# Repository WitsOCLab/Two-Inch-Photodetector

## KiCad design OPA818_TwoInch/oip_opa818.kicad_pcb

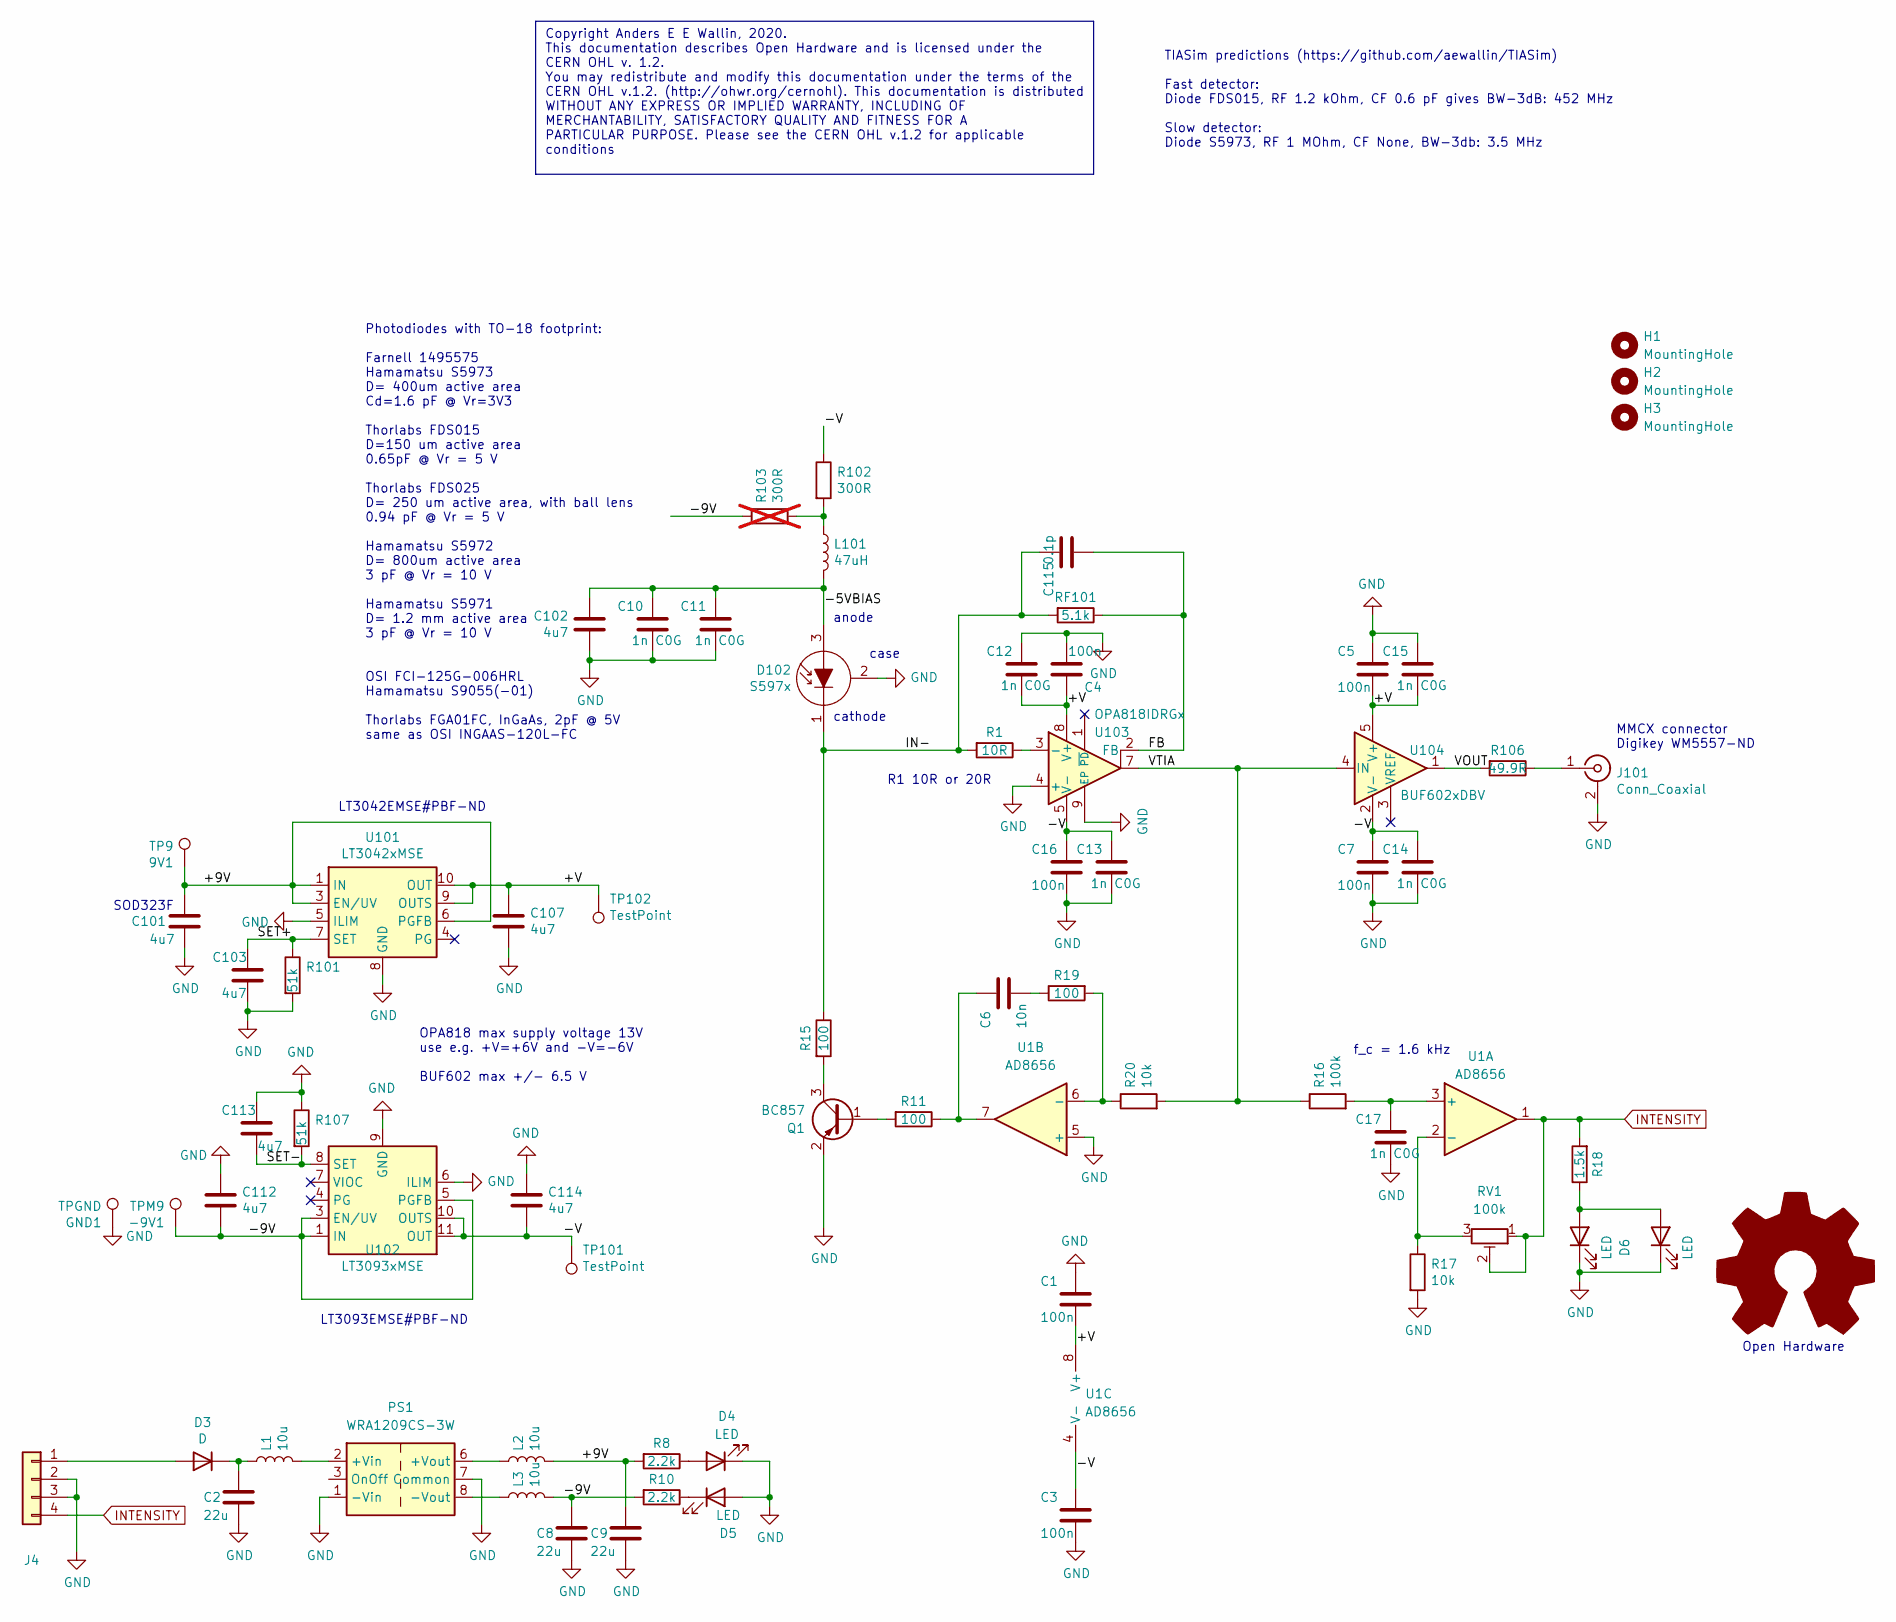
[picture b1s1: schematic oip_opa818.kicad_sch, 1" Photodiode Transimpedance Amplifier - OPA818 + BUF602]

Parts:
9V1: TP9; TestPoint_THTPad_D1.0mm_Drill0.5mm
-9V1: TPM9; TestPoint_THTPad_D1.0mm_Drill0.5mm
C1, C3, C4, C5, C7, C16: 100n; C_0402_1005Metric; JLCPCB C307331
C2, C8, C9: 22u; C_0805_2012Metric; JLCPCB C45783
C6: 10n; C_0402_1005Metric; LCSC C15195
C10, C11, C12, C13, C14, C15, C17: 1n C0G; C_0402_1005Metric; JLCPCB C76947
C101, C102, C103, C107, C112, C113, C114: 4u7; C_0603_1608Metric; JLCPCB C19666
C115: 0.1p; C_0402_1005Metric; LCSC C53273
D3: D; D_SOD-323F; JLCPCB C191023
D4, D5, D6, D7: LED; LED_0603_1608Metric; JLCPCB C72043
D102: S597x; TO-18-3
GND1: TPGND; TestPoint_THTPad_D1.0mm_Drill0.5mm
H1, H2, H3: MountingHole; MountingHole_3.2mm_M3_DIN965_Pad_TopBottom
J4: PinHeader_1x04_P2.54mm_Vertical
J101: Conn_Coaxial; MMCX_Molex_73415-1471_Vertical; JLCPCB C530664
L1, L2, L3: 10u; L_0805_2012Metric; JLCPCB C281113
L101: 47uH; L_0805_2012Metric; LCSC C404762
PS1: WRA1209CS-3W; Converter_DCDC_XP_POWER-ITQxxxxS-H_THT; LCSC C512079
Q1: BC857; SOT-323_SC-70; LCSC C8660
R1: 10R; R_0402_1005Metric; JLCPCB C25077
R8, R10: 2.2k; R_0402_1005Metric; JLCPCB C25879
R11, R15, R19: 100; R_0402_1005Metric; JLCPCB C25076
R16: 100k; R_0402_1005Metric; LCSC C25741
R17, R20: 10k; R_0402_1005Metric; LCSC C25744
R18: 1.5k; R_0603_1608Metric; LCSC C22843
R101, R107: 51k; R_0603_1608Metric; JLCPCB C23186
R102: 300R; R_0603_1608Metric; JLCPCB C23025
R103: 300R; R_0603_1608Metric; JLCPCB C23025; not fitted
R106: 49.9R; R_0402_1005Metric; JLCPCB C25120
RF101: 5.1k; R_0402_1005Metric; JLCPCB C351692
RV1: 100k; Potentiometer_Bourns_TC33X_Vertical; LCSC C719186
TP101, TP102: TestPoint; TestPoint_THTPad_D1.0mm_Drill0.5mm
U1: AD8656; MSOP-8_3x3mm_P0.65mm; LCSC C208582
U101: LT3042xMSE; MSOP-10-1EP_3x3mm_P0.5mm_EP1.68x1.88mm; LCSC C69847
U102: LT3093xMSE; MSOP-12-1EP_3x4mm_P0.65mm_EP1.65x2.85mm; LCSC C670490
U103: OPA818IDRGx; WSON-8-1EP_3x3mm_P0.5mm_EP1.45x2.4mm; JLCPCB C2859543
U104: BUF602xDBV; SOT-23-5; LCSC C2862949

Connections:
/+9V: 9V1.1, C9.1, C101.1, L2.2, R8.2, U101.1 (IN), U101.2 (IN), U101.3 (EN/UV), U101.6 (PGFB)
/+V: C1.2, C4.1, C5.2, C12.2, C15.2, C107.1, TP102.1, U1.8 (V+), U101.9 (OUTS), U101.10 (OUT), U103.8 (V+), U104.5 (V+)
/-5VBIAS: C10.1, C11.1, C102.1, D102.3 (A), L101.2
/-9V: -9V1.1, C8.1, C112.2, L3.2, R10.2, R103.1, U102.1 (IN), U102.2 (IN), U102.3 (EN/UV), U102.5 (PGFB), U102.13 (IN)
/-V: C3.1, C7.1, C13.1, C14.1, C16.1, C114.2, R102.1, TP101.1, U1.4 (V-), U102.10 (OUTS), U102.11 (OUT), U102.12 (OUT), U103.5 (V-), U104.2 (V-)
/FB: C115.1, RF101.1, U103.2 (FB)
/IN-: C115.2, D102.1 (K), R1.2, R15.1, RF101.2
/SET+: C103.1, R101.1, U101.7 (SET)
/SET-: C113.2, R107.2, U102.8 (SET)
/VOUT: R106.2, U104.1
/VTIA: R16.1, R20.2, U103.7, U104.4 (IN)
GND: C1.1, C2.2, C3.2, C4.2, C5.1, C7.2, C8.2, C9.2, C10.2, C11.2, C12.1, C13.2, C14.2, C15.1, C16.2, C17.2, C101.2, C102.2, C103.2, C107.2, C112.1, C113.1, C114.1, D4.1 (K), D5.2 (A), D6.1 (K), D7.1 (K), D102.2 (C), GND1.1, J4.2, J4.3, J101.2 (Ext), PS1.1 (-Vin), PS1.7 (Common), Q1.2 (E), R17.2, R101.2, R107.1, U1.5 (+), U101.5 (ILIM), U101.8 (GND), U101.11 (GND), U102.6 (ILIM), U102.9 (GND), U103.4 (+), U103.9 (EP)
INTENSITY: J4.4, R18.2, RV1.1, RV1.2, U1.1
unnamed: C6.1, R11.1, U1.7
unnamed: C6.2, R19.1
unnamed: D3.2 (A), J4.1
unnamed: C2.1, D3.1 (K), L1.1
unnamed: D4.2 (A), R8.1
unnamed: D5.1 (K), R10.1
unnamed: D6.2 (A), D7.2 (A), R18.1
unnamed: J101.1 (In), R106.1
unnamed: L101.1, R102.2, R103.2
unnamed: L1.2, PS1.2 (+Vin)
unnamed: L2.1, PS1.6 (+Vout)
unnamed: L3.1, PS1.8 (-Vout)
unnamed: Q1.1 (B), R11.2
unnamed: Q1.3 (C), R15.2
unnamed: C17.1, R16.2, U1.3 (+)
unnamed: R17.1, RV1.3, U1.2 (-)
unnamed: R19.2, R20.1, U1.6 (-)
unnamed: R1.1, U103.3 (-)

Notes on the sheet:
LT3042EMSE#PBF-ND
TIASim predictions (https://github.com/aewallin/TIASim) Fast detector: Diode FDS015, RF 1.2 kOhm, CF 0.6 pF gives BW-3dB: 452 MHz Slow detector: Diode S5973, RF 1 MOhm, CF None, BW-3db: 3.5 MHz
cathode
MMCX connector Digikey WM5557-ND
case
R1 10R or 20R
Open Hardware
Photodiodes with TO-18 footprint: Farnell 1495575 Hamamatsu S5973 D= 400um active area Cd=1.6 pF @ Vr=3V3 Thorlabs FDS015 D=150 um active area 0.65pF @ Vr = 5 V Thorlabs FDS025 D= 250 um active area, with ball lens 0.94 pF @ Vr = 5 V Hamamatsu S5972 D= 800um active area 3 pF @ Vr = 10 V Hamamatsu S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
OPA818 max supply voltage 13V use e.g. +V=+6V and -V=-6V BUF602 max +/- 6.5 V
Copyright Anders E E Wallin, 2020. This documentation describes Open Hardware and is licensed under the CERN OHL v. 1.2. You may redistribute and modify this documentation under the terms of the CERN OHL v.1.2. (http://ohwr.org/cernohl). This documentation is distributed WITHOUT ANY EXPRESS OR IMPL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
f_c = 1.6 kHz
anode
LT3093EMSE#PBF-ND
SOD323F

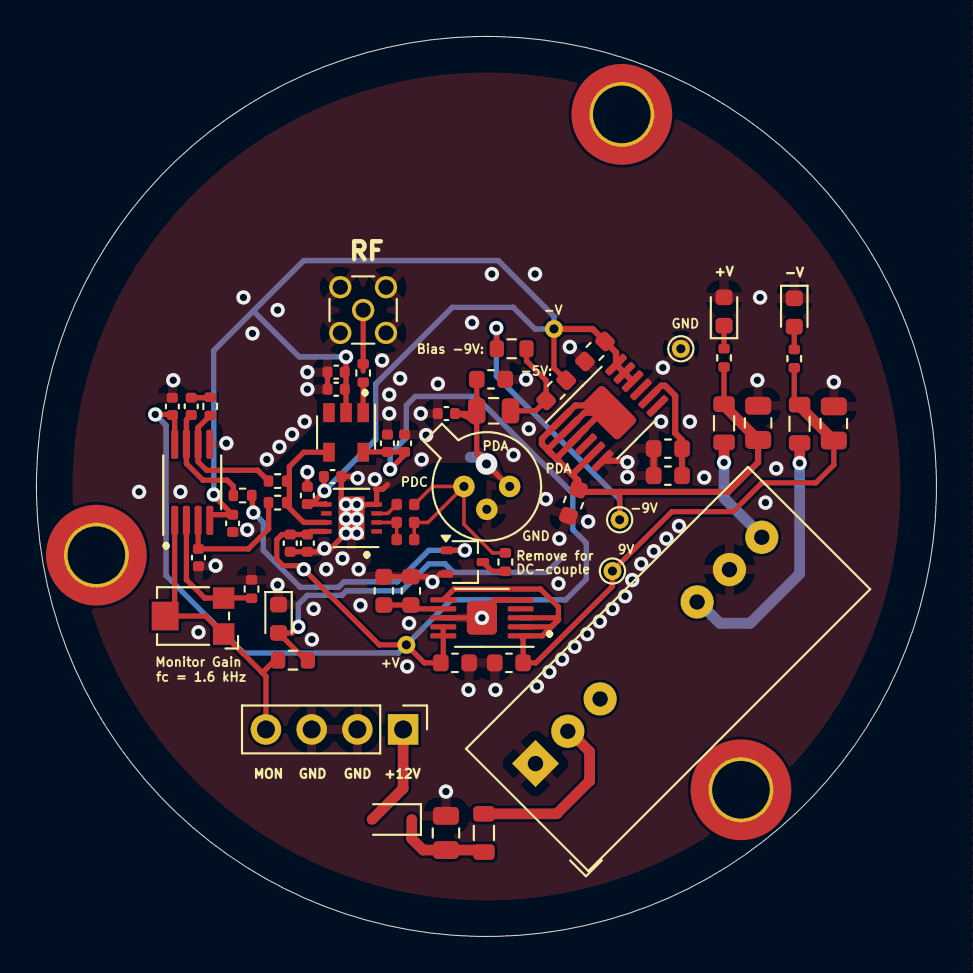
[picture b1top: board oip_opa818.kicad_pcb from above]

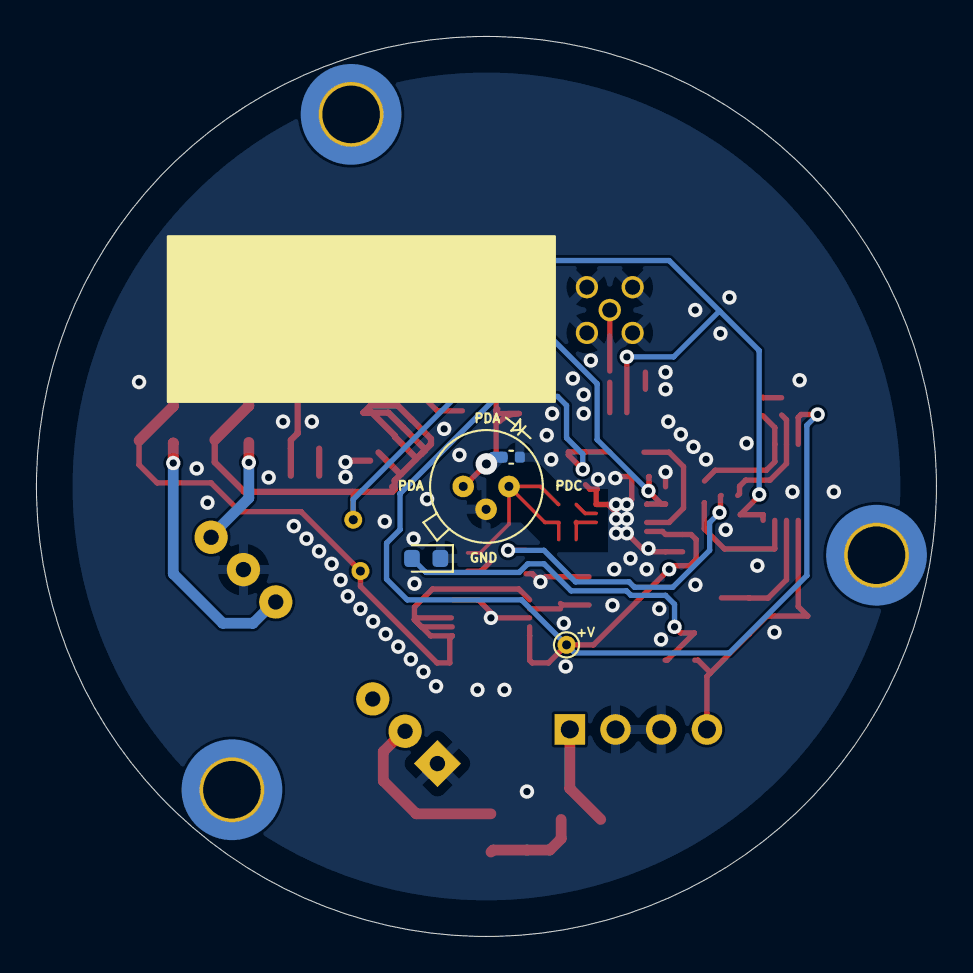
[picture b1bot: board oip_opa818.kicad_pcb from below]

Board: 2 copper layers, 50.0 x 50.0 mm, 69 parts (4 on the bottom side), 31 nets.

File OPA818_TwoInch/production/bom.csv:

Designator,Footprint,Quantity,Value,LCSC Part #
-9V1,TestPoint_THTPad_D1.0mm_Drill0.5mm,1,TPM9,
9V1,TestPoint_THTPad_D1.0mm_Drill0.5mm,1,TP9,
"C1, C16, C3, C4, C5, C7",0402,6,100n,C307331
"C10, C11, C12, C13, C14, C15, C17",0402,7,1n C0G,C76947
"C101, C102, C103, C107, C112, C113, C114",0603,7,4u7,C19666
C115,0402,1,0.1p,C53273
"C2, C8, C9",0805,3,22u,C45783
C6,0402,1,10n,C15195
D102,TO-18-3,1,S597x,
D3,D_SOD-323F,1,D,C191023
"D4, D5, D6, D7",0603,4,LED,C72043
GND1,TestPoint_THTPad_D1.0mm_Drill0.5mm,1,TPGND,
J101,MMCX_Molex_73415-1471_Vertical,1,Conn_Coaxial,C530664
J4,PinHeader_1x04_P2.54mm_Vertical,1,~,
"L1, L2, L3",0805,3,10u,C281113
L101,0805,1,47uH,C404762
PS1,Converter_DCDC_XP_POWER-ITQxxxxS-H_THT,1,WRA1209CS-3W,C512079
Q1,SOT-323_SC-70,1,BC857,C8660
R1,0402,1,10R,C25077
"R10, R8",0402,2,2.2k,C25879
"R101, R107",0603,2,51k,C23186
R102,0603,1,300R,C23025
R106,0402,1,49.9R,C25120
"R11, R15, R19",0402,3,100,C25076
R16,0402,1,100k,C25741
"R17, R20",0402,2,10k,C25744
R18,0603,1,1.5k,C22843
RF101,0402,1,5.1k,C351692
RV1,Potentiometer_Bourns_TC33X_Vertical,1,100k,C719186
"TP101, TP102",TestPoint_THTPad_D1.0mm_Drill0.5mm,2,TestPoint,
U1,MSOP-8_3x3mm_P0.65mm,1,AD8656,C208582
U101,MSOP-10-1EP_3x3mm_P0.5mm_EP1.68x1.88mm,1,LT3042xMSE,C69847
U102,MSOP-12-1EP_3x4mm_P0.65mm_EP1.65x2.85mm,1,LT3093xMSE,C670490
U103,WSON-8-1EP_3x3mm_P0.5mm_EP1.45x2.4mm,1,OPA818IDRGx,C2859543
U104,SOT-23-5,1,BUF602xDBV,C2862949

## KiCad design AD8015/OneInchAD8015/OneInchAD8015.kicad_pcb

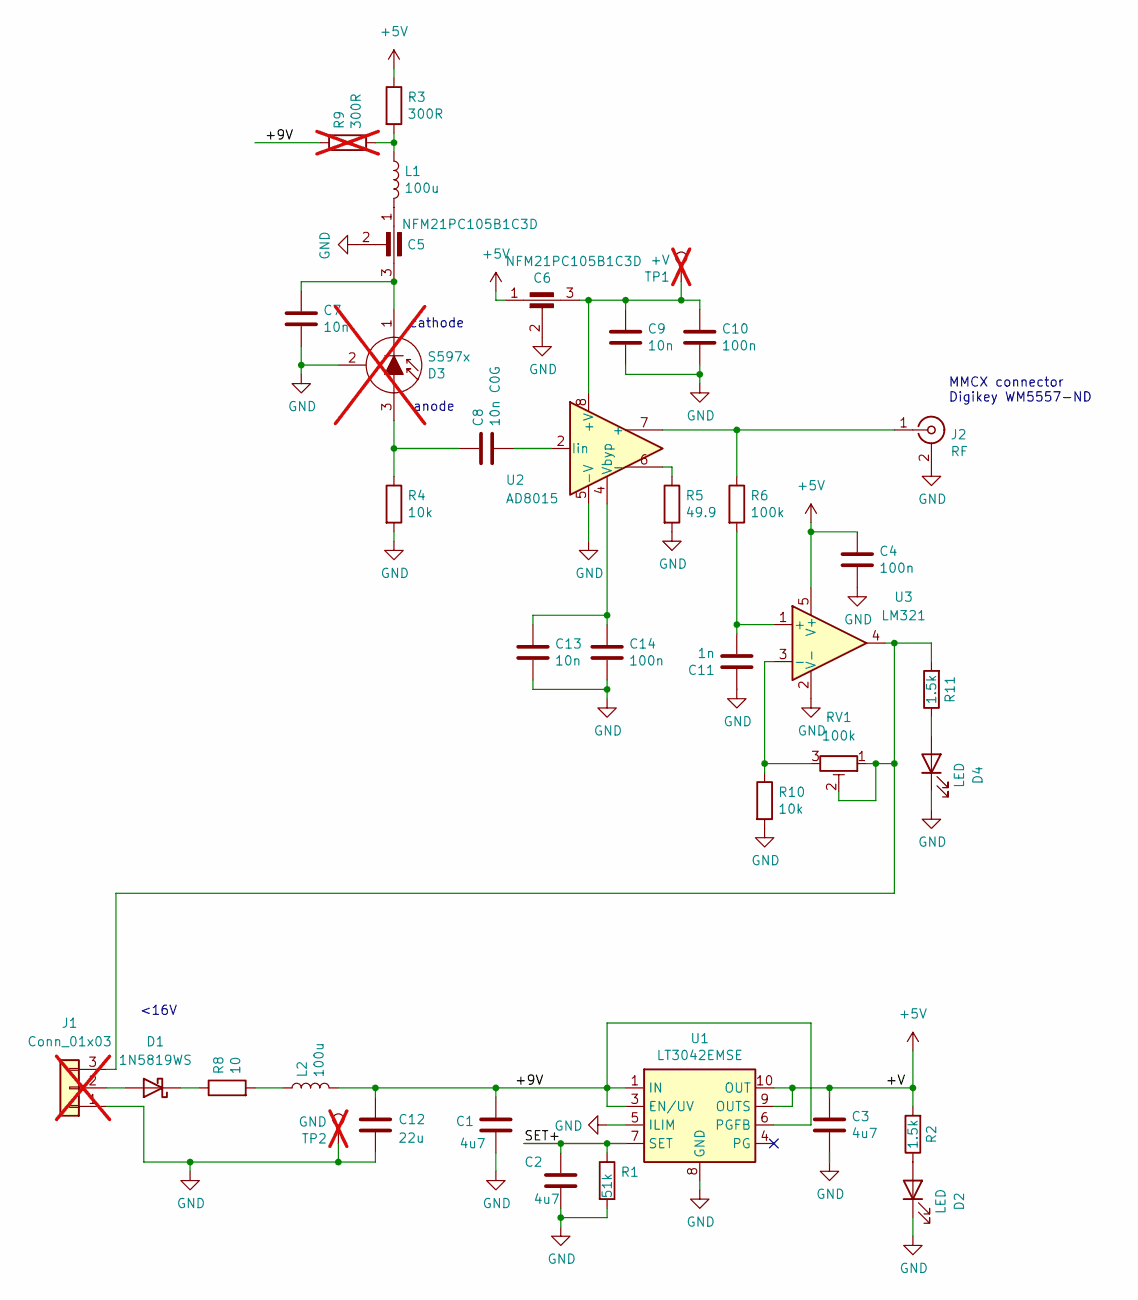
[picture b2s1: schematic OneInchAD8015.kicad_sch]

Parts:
C1, C2, C3: 4u7; C_0603_1608Metric; JLCPCB C19666
C4, C10, C14: 100n; C_0402_1005Metric; JLCPCB C1525
C5, C6: NFM21PC105B1C3D; NFM21C; LCSC C92518
C7, C9, C13: 10n; C_0402_1005Metric; JLCPCB C15195
C8: 10n C0G; C_0603_1608Metric; JLCPCB C76710
C11: 1n; C_0402_1005Metric; LCSC C1523
C12: 22u; C_0805_2012Metric; JLCPCB C45783
D1: 1N5819WS; D_SOD-323; LCSC C191023
D2, D4: LED; LED_0603_1608Metric; JLCPCB C72043
D3: S597x; TO-18-3; not fitted
J1: Conn_01x03; PinHeader_1x03_P2.00mm_Vertical; not fitted
J2: RF; MMCX_Molex_73415-1471_Vertical; JLCPCB C530664
L1, L2: 100u; L_0805_2012Metric; JLCPCB C68035
R1: 51k; R_0603_1608Metric; JLCPCB C23186
R2: 1.5k; R_0603_1608Metric; JLCPCB C25879
R3: 300R; R_0603_1608Metric; JLCPCB C23025
R4, R10: 10k; R_0402_1005Metric; LCSC C25744
R5: 49.9; R_0402_1005Metric; LCSC C325388
R6: 100k; R_0402_1005Metric; LCSC C25741
R8: 10; R_0603_1608Metric; JLCPCB C22859
R9: 300R; R_0603_1608Metric; not fitted
R11: 1.5k; R_0603_1608Metric; JLCPCB C21190
RV1: 100k; Potentiometer_Bourns_TC33X_Vertical; LCSC C719186
TP1: +V; TestPoint_THTPad_D1.0mm_Drill0.5mm; not fitted
TP2: GND; TestPoint_THTPad_D1.0mm_Drill0.5mm; not fitted
U1: LT3042EMSE; MSOP-10-1EP_3x3mm_P0.5mm_EP1.68x1.88mm; LCSC C69847
U2: AD8015; SOIC-8_3.9x4.9mm_P1.27mm; LCSC C514255
U3: LM321; SOT-23-5; LCSC C471859

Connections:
+5V: C3.1, C4.1, C6.1, R2.2, R3.1, U1.9 (OUTS), U1.10 (OUT), U3.5 (V+)
/+9V: C1.1, C12.1, L2.2, R9.1, U1.1 (IN), U1.2 (IN), U1.3 (EN/UV), U1.6 (PGFB)
/SET+: C2.1, R1.1, U1.7 (SET)
GND: C1.2, C2.2, C3.2, C4.2, C5.2, C6.2, C7.2, C9.2, C10.2, C11.1, C12.2, C13.2, C14.2, D2.1 (K), D3.2 (C), D4.1 (K), J1.1, J2.2 (Ext), R1.2, R4.2, R5.2, R10.2, TP2.1, U1.5 (ILIM), U1.8 (GND), U1.11 (GND), U2.5 (-V), U3.2 (V-); also elsewhere on the board
unnamed: C5.1, L1.2
unnamed: D1.2 (A), J1.2
unnamed: D1.1 (K), R8.1
unnamed: D2.2 (A), R2.1
unnamed: C8.1, D3.3 (A), R4.1
unnamed: C5.3, C7.1, D3.1 (K)
unnamed 10: D4.2 (A), R11.1; also elsewhere on the board
unnamed: J1.3, R11.2, RV1.1, RV1.2, U3.4
unnamed: J2.1 (In), R6.1, U2.7 (+)
unnamed: L1.1, R3.2, R9.2
unnamed: L2.1, R8.2
unnamed: C6.3, C9.1, C10.1, TP1.1, U2.8 (+V)
unnamed: R5.1, U2.6 (-)
unnamed: C8.2, U2.2 (Iin)
unnamed: C13.1, C14.1, U2.4 (Vbyp)
unnamed: C11.2, R6.2, U3.1 (+)
unnamed: R10.1, RV1.3, U3.3 (-)

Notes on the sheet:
<16V
anode
MMCX connector Digikey WM5557-ND
cathode

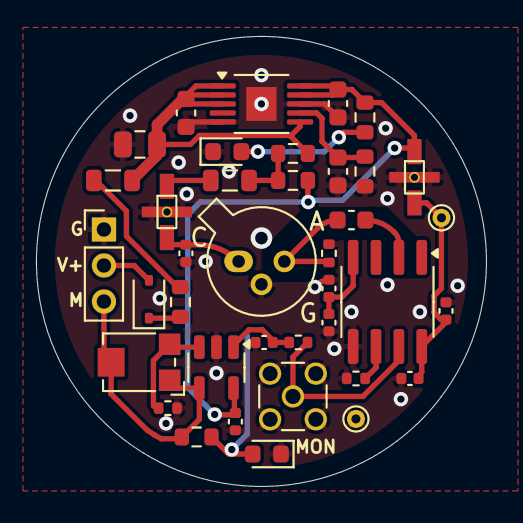
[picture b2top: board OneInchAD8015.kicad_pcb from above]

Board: 2 copper layers, 25.0 x 25.0 mm, 39 parts (1 on the bottom side), 21 nets.

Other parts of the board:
D5: LED; LED_0603_1608Metric

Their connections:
GND: D5.1 (K); also elsewhere on the board
unnamed 10: D5.2 (A); also elsewhere on the board

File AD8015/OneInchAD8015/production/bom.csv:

Designator,Footprint,Quantity,Value,LCSC Part #
"C1, C2, C3",0603,3,4u7,C19666
"C10, C14, C4",0402,3,100n,C1525
C11,0402,1,1n,C1523
C12,0805,1,22u,C45783
"C13, C7, C9",0402,3,10n,C15195
"C5, C6",NFM21C,2,NFM21PC105B1C3D,C92518
C8,0603,1,10n C0G,C76710
D1,D_SOD-323,1,1N5819WS,C191023
"D2, D4",0603,2,LED,C72043
J2,MMCX_Molex_73415-1471_Vertical,1,RF,C530664
"L1, L2",0805,2,100u,C68035
R1,0603,1,51k,C23186
"R10, R4",0402,2,10k,C25744
"R11, R2",0603,2,1.5k,C22843
R3,0603,1,300R,C23025
R5,0402,1,49.9,C325388
R6,0402,1,100k,C25741
R8,0603,1,10,C22859
RV1,Potentiometer_Bourns_TC33X_Vertical,1,100k,C719186
U1,MSOP-10-1EP_3x3mm_P0.5mm_EP1.68x1.88mm,1,LT3042EMSE,C69847
U2,SOIC-8_3.9x4.9mm_P1.27mm,1,AD8015,C514255
U3,SOT-23-5,1,LM321,C471859

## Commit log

2023-05-30 2 inch version
2023-12-30 v1 for jlc
2025-01-06 v1 of OneInchAD8015
2025-01-06 labels
2025-01-13 pot for mon
2025-03-28 mods
2025-03-28 gerbers
2025-04-06 seems to be done, ac coupled
2025-04-06 garbage
2025-04-28 finished?
